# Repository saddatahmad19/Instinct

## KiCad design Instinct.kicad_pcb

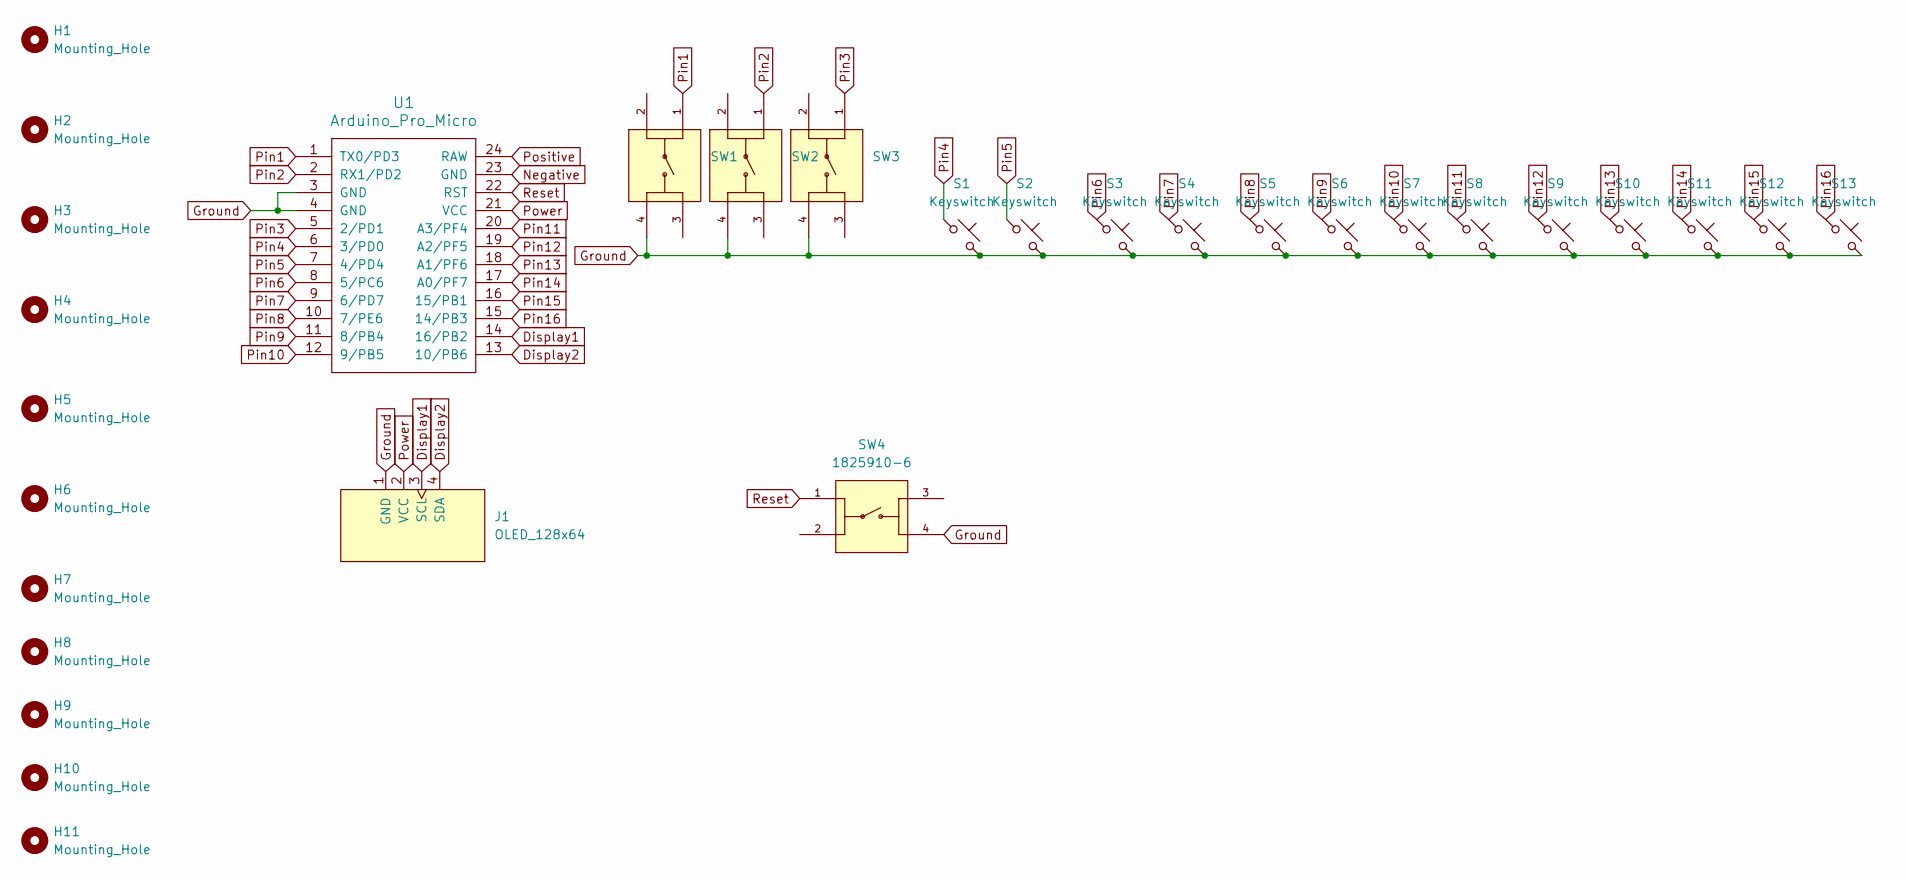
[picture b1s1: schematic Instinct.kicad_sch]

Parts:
H1, H2, H3, H4, H5, H6, H7, H8, H9, H10, H11: Mounting_Hole; MountingHole_2mm
J1: OLED_128x64
S1, S2, S3, S4, S5, S6, S7, S8, S9, S10, S11, S12, S13: Keyswitch; Hotswap_MX_1.00u
SW1, SW2, SW3, SW4: 1825910-6; SW_1825910-6-4; PARTREV C10
U1: Arduino_Pro_Micro

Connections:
Display1: J1.3 (SCL), U1.14 (16/PB2)
Display2: J1.4 (SDA), U1.13 (10/PB6)
Ground: J1.1 (GND), S1.2, S2.2, S3.2, S4.2, S5.2, S6.2, S7.2, S8.2, S9.2, S10.2, S11.2, S12.2, S13.2, SW1.4, SW2.4, SW3.4, SW4.4, U1.3 (GND), U1.4 (GND)
Negative: U1.23 (GND)
Pin1: SW1.1, U1.1 (TX0/PD3)
Pin2: SW2.1, U1.2 (RX1/PD2)
Pin3: SW3.1, U1.5 (2/PD1)
Pin4: S1.1, U1.6 (3/PD0)
Pin5: S2.1, U1.7 (4/PD4)
Pin6: S3.1, U1.8 (5/PC6)
Pin7: S4.1, U1.9 (6/PD7)
Pin8: S5.1, U1.10 (7/PE6)
Pin9: S6.1, U1.11 (8/PB4)
Pin10: S7.1, U1.12 (9/PB5)
Pin11: S8.1, U1.20 (A3/PF4)
Pin12: S9.1, U1.19 (A2/PF5)
Pin13: S10.1, U1.18 (A1/PF6)
Pin14: S11.1, U1.17 (A0/PF7)
Pin15: S12.1, U1.16 (15/PB1)
Pin16: S13.1, U1.15 (14/PB3)
Positive: U1.24 (RAW)
Power: J1.2 (VCC), U1.21 (VCC)
Reset: SW4.1, U1.22 (RST)

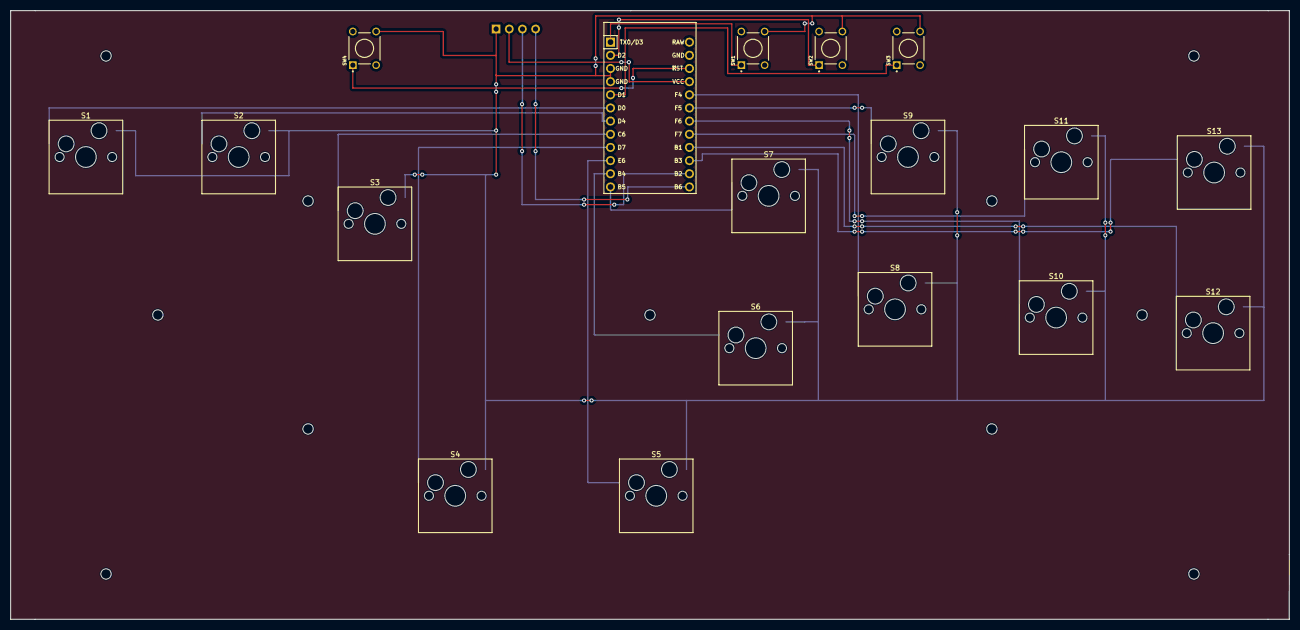
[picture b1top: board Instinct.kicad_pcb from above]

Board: 2 copper layers, 246.9 x 117.5 mm, 30 parts (0 on the bottom side), 21 nets.

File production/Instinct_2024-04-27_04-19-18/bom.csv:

Designator,Footprint,Quantity,Value,LCSC Part #
"H1, H10, H11, H2, H3, H4, H5, H6, H7, H8, H9",MountingHole_2mm,11,Mounting_Hole,
J1,OLED_128x64,1,OLED_128x64,
"S1, S10, S11, S12, S13, S2, S3, S4, S5, S6, S7, S8, S9",Hotswap_MX_1.00u,13,Keyswitch,
"SW1, SW2, SW3, SW4",SW_1825910-6-4,4,1825910-6,
U1,Arduino_Pro_Micro,1,Arduino_Pro_Micro,

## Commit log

2024-04-27 Big Update
2024-04-27 more touches
2024-04-27 Made a front plate
    this will go in between the top case and the pcb
